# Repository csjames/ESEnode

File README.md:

# ESEnode

* 868 Mhz radio and LoRa development board
* MBED Compatible
* RGB LED
* Full Bill of Materials

# Radio Modules Compatible

## RFM69HW (868 FSK)

## RFM95 (LoRa)

# Bill of Materials

| Part                                                                                                                 	| Price 	| Quantity |
|----------------------------------------------------------------------------------------------------------------------	|-------	| ---------|
| **[LPC11U68](http://onecall.farnell.com/nxp/lpc11u68jbd48e/mcu-32bit-cortex-m0-50mhz-lqfp/dp/2433462)**              	| 2.61  	| 1|
| **[RFM69HW](http://onecall.farnell.com/hoperf/rfm69hw-868s2/transceiver-20dbm-116dbm-868mhz/dp/RF00489)**            	| 6.67  	| 1|
| **[RFM95W](http://onecall.farnell.com/hoperf/rfm95w-868s2/lora-transceiver-module-20dbm/dp/RF00490)**                 | 13.56   | 1|
| **[RGB LED PLCC-4](http://onecall.farnell.com/broadcom-limited/asmb-mtb1-0a3a2/led-hb-rgb-0-09w-plcc-4/dp/2401106)** 	| 0.12  	| 1|
| **[10Ω 0603](http://onecall.farnell.com/multicomp/mc0063w0603110r/res-thick-film-10r-1-0-063w-0603/dp/9330429)**|0.10 (x100)|2|
| **[10uF 0603](http://onecall.farnell.com/multicomp/mcca000180/mlcc-0603-y5v-25v-1uf/dp/CA06409)**|1.00 (x100)|1|                                	|       	| 1|
| **[Micro USB A/B Female](http://onecall.farnell.com/molex/47589-0001/micro-usb-2-0-type-ab-receptacle/dp/1568023)**|0.32|1|
| **TOTAL** | **10.81/17.71**(RFM69/95) | - |

### Designed by Joshua Curry and James Adams

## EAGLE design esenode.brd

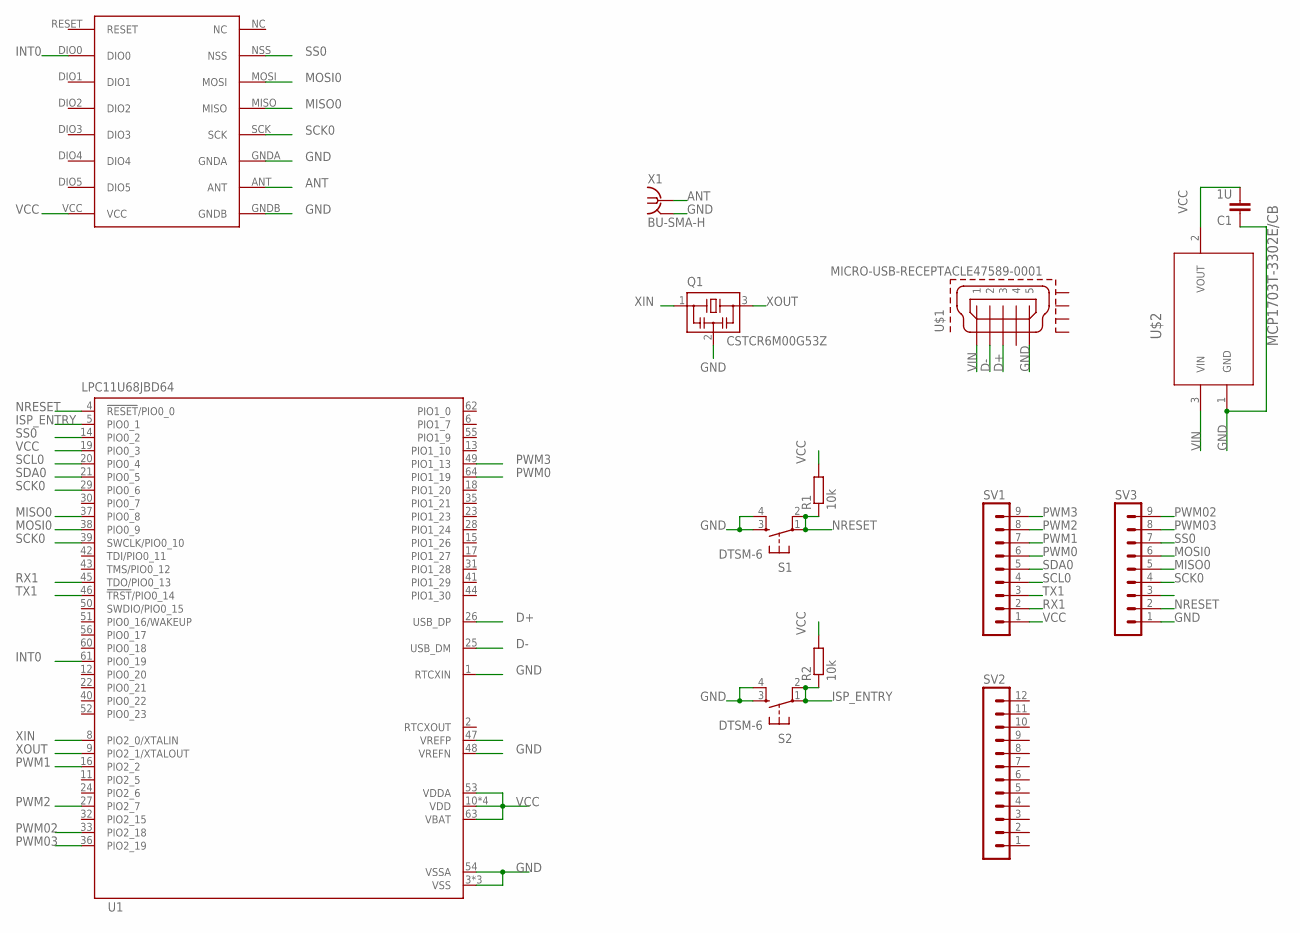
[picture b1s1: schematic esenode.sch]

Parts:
C1: 1U; C0805
Q1: CSTCR6M00G53Z; CSTCR6M
R1, R2: 10k; M0805
S1, S2: DTSM-6
SV1, SV3: MA09-1
SV2: MA12-1
U1: LPC11U68JBD64; SOT314-2
U$1: MICRO-USB-RECEPTACLE47589-0001; 47589-0001
U$2: MCP1703T-3302E/CB; SOT95P300X145-3N
U$3: RFM69HW; RFM
X1: BU-SMA-H

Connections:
ANT: U$3.ANT, X1.1
D+: U1.26 (USB_DP), U$1.3
D-: U1.25 (USB_DM), U$1.2
GND: C1.1, Q1.2, S1.3, S1.4, S2.3, S2.4, SV3.1, U1.1 (RTCXIN), U1.3 (VSS), U1.7 (VSS), U1.48 (VREFN), U1.54 (VSSA), U1.57 (VSS), U$1.5, U$2.1 (GND), U$3.GNDA, U$3.GNDB, X1.2, X1.3 (2), X1.4 (2), X1.5 (2)
INT0: U1.61 (PIO0_19), U$3.DIO0
ISP_ENTRY: R2.1, S2.1, S2.2, U1.5 (PIO0_1)
MISO0: SV3.5, U1.37 (PIO0_8), U$3.MISO
MOSI0: SV3.6, U1.38 (PIO0_9), U$3.MOSI
NRESET: R1.1, S1.1, S1.2, SV3.2, U1.4 (!RESET!/PIO0_0)
PWM0: SV1.6, U1.64 (PIO1_19)
PWM1: SV1.7, U1.16 (PIO2_2)
PWM2: SV1.8, U1.27 (PIO2_7)
PWM02: SV3.9, U1.33 (PIO2_18)
PWM3: SV1.9, U1.49 (PIO1_13)
PWM03: SV3.8, U1.36 (PIO2_19)
RX1: SV1.2, U1.45 (TDO/PIO0_13)
SCK0: SV3.4, U1.29 (PIO0_6), U1.39 (SWCLK/PIO0_10), U$3.SCK
SCL0: SV1.4, U1.20 (PIO0_4)
SDA0: SV1.5, U1.21 (PIO0_5)
SS0: SV3.7, U1.14 (PIO0_2), U$3.NSS
TX1: SV1.3, U1.46 (!TRST!/PIO0_14)
VCC: C1.2, R1.2, R2.2, SV1.1, U1.10 (VDD), U1.19 (PIO0_3), U1.34 (VDD), U1.53 (VDDA), U1.58 (VDD), U1.59 (VDD), U1.63 (VBAT), U$2.2 (VOUT), U$3.VCC
VIN: U$1.1, U$2.3 (VIN)
XIN: Q1.1, U1.8 (PIO2_0/XTALIN)
XOUT: Q1.3, U1.9 (PIO2_1/XTALOUT)

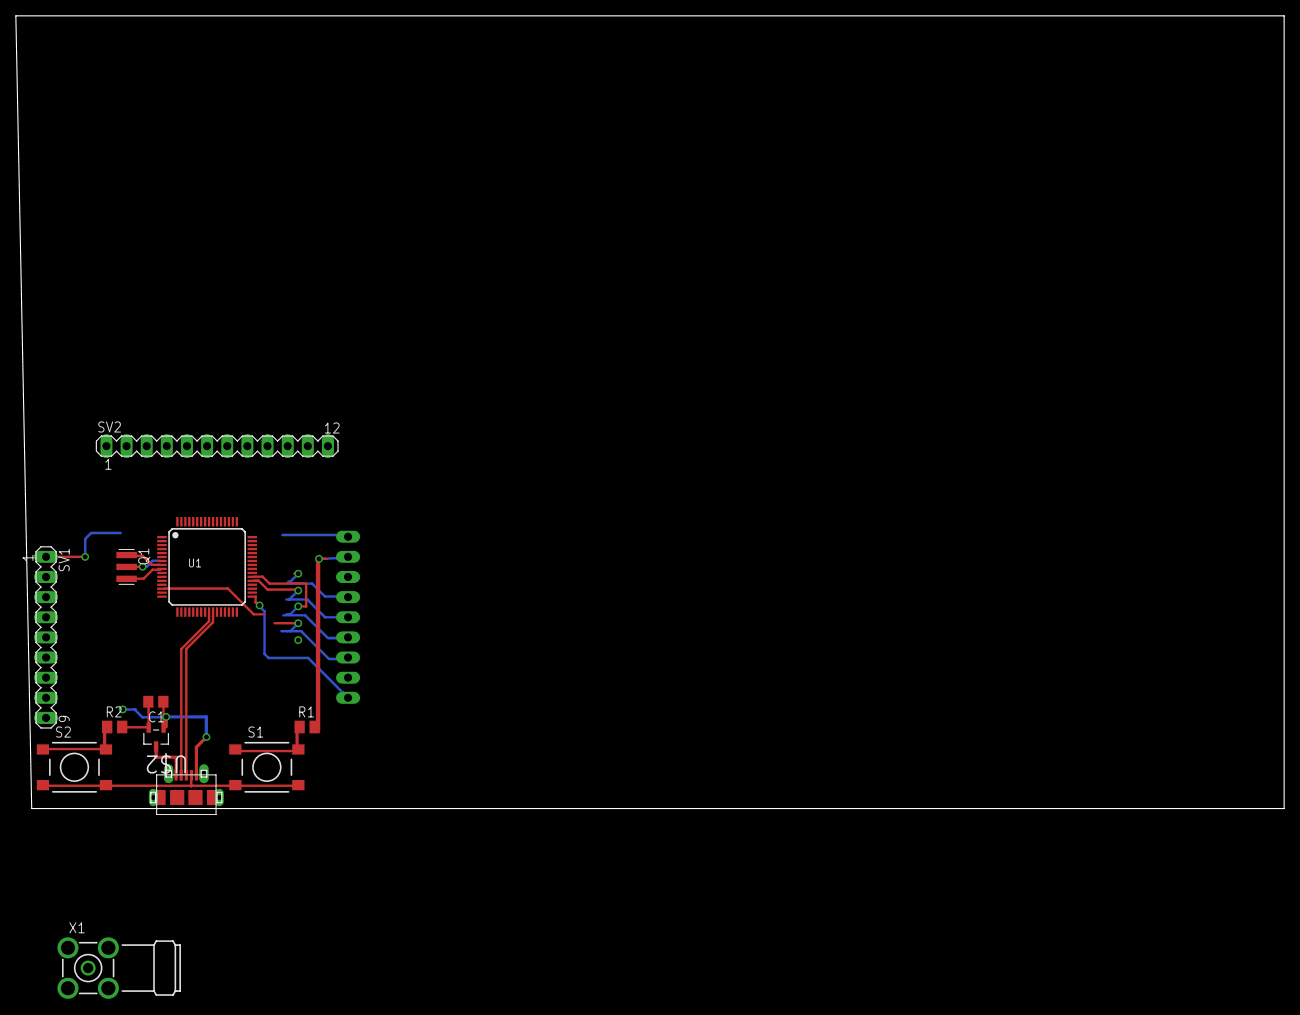
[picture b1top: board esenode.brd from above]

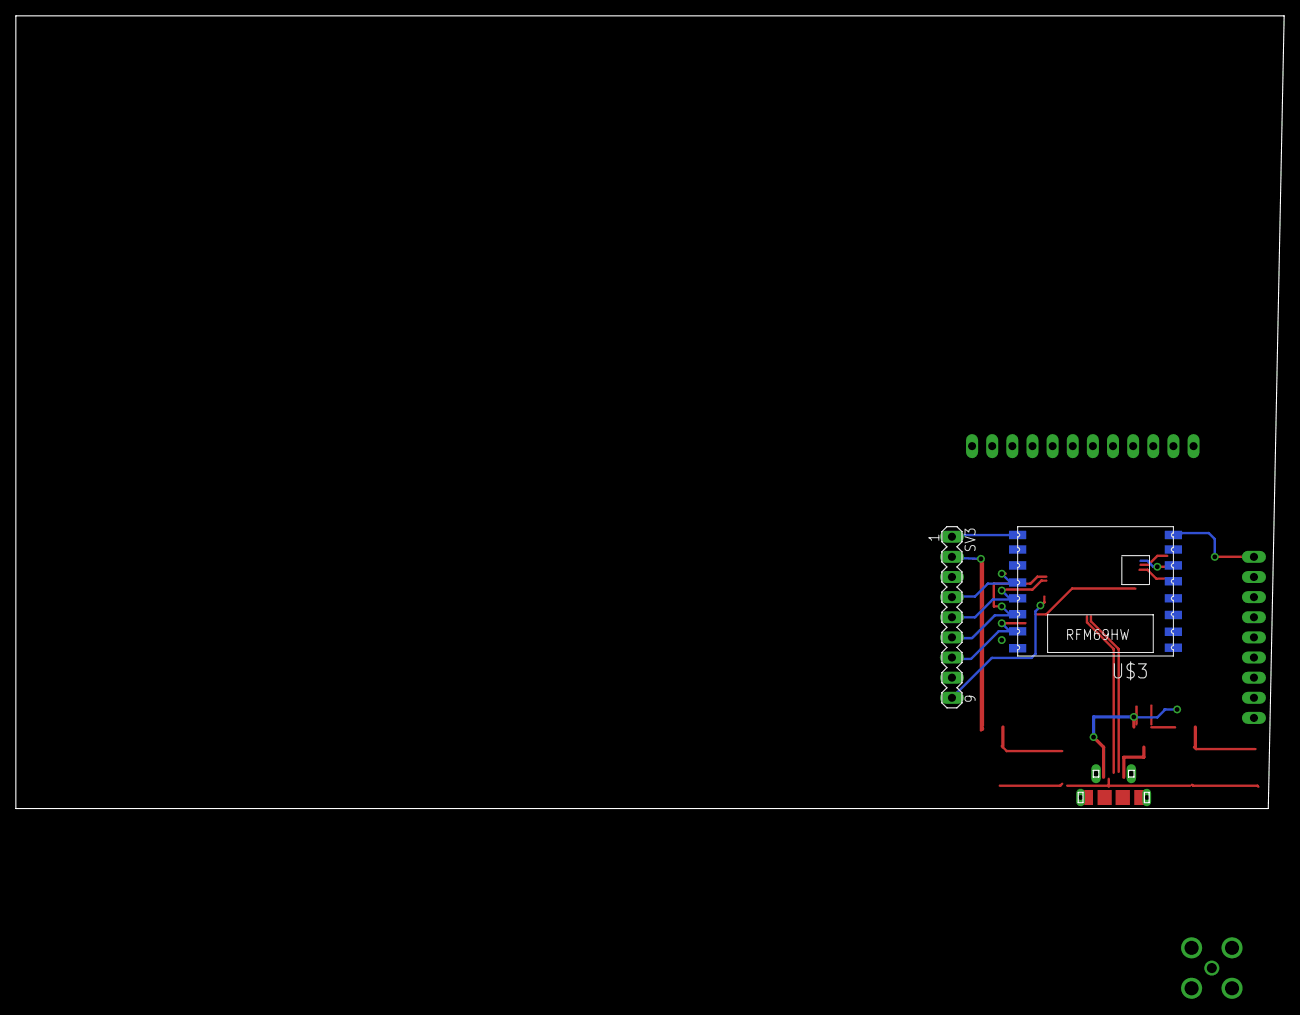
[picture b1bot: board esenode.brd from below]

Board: 2 copper layers, 160.0 x 100.0 mm, 14 parts (2 on the bottom side), 25 nets.

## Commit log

2017-02-11 added libraries and board draft
2017-02-11 Set theme jekyll-theme-midnight
2017-02-12 Added RFM95W LoRa module
2017-02-12 y u do dis
2017-04-04 #challenge, then connect gpio to top bar and see if still possible lol
2017-04-04 added antenna

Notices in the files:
parts and their libraries:
con-molex-usb: (C) 2014 Tomasz Boleslaw CEDRO, cederom@tlen.pl, http://www.tomek.cedro.info.
NXP_60_26022015: This library may be distributed and adapted freely for any purpose, as long as NXP is credited and any new creation is licensed under the same terms.
